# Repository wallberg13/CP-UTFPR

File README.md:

# CP-UTFPR

Este repositório é destinado a guardar todos os trabalhos e códigos
desenvolvidos ao longo da minha graduação em Engenharia de Computação na
UTFPR-PB.

> Pastas desorganizadas pois a organização veio com o tempo e o repositório
> ainda está um pouco bagunçando, mas com o tempo melhora.

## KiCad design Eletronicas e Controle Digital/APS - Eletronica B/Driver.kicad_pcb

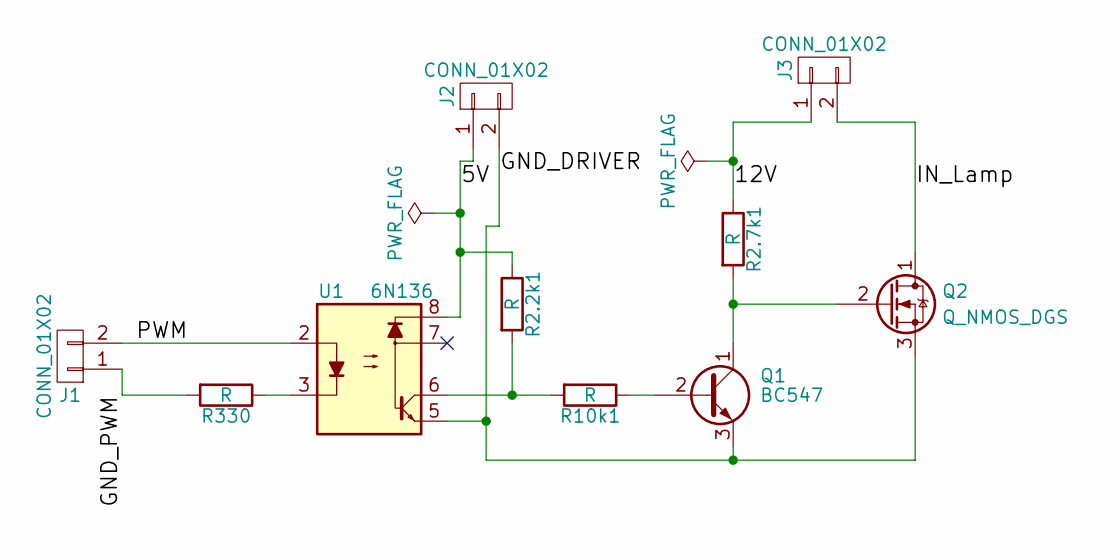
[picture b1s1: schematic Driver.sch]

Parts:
J1, J2, J3: CONN_01X02; bornier2
Q1: BC547; TO-92_Inline_Wide
Q2: Q_NMOS_DGS; Wafer_Vertical10x5.8x7RM2.5-3
R2.2k1, R2.7k1, R10k1, R330: R; R_Axial_DIN0309_L9.0mm_D3.2mm_P12.70mm_Horizontal
U1: 6N136; DIP-8_W7.62mm_Socket_LongPads

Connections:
/5V: J2.1, R2.2k1.1, U1.8
/12V: J3.1, R2.7k1.1
/GND_DRIVER: J2.2, Q1.3 (E), Q2.3 (S), U1.5
/GND_PWM: J1.1, R330.2
/IN_Lamp: J3.2, Q2.1 (D)
/PWM: J1.2, U1.2
unnamed: Q1.1 (C), Q2.2 (G), R2.7k1.2
unnamed: Q1.2 (B), R10k1.1
unnamed: R2.2k1.2, R10k1.2, U1.6
unnamed: R330.1, U1.3

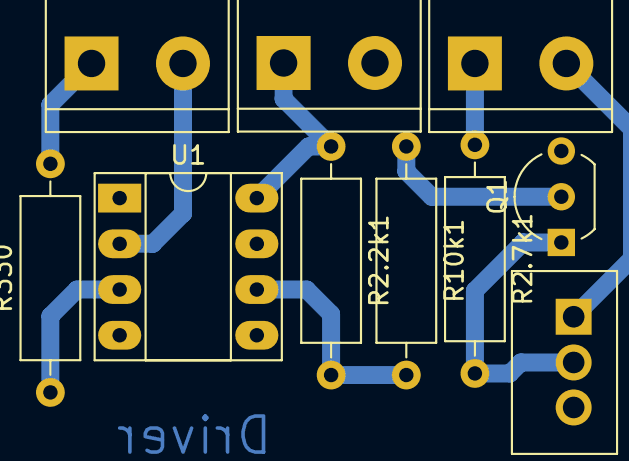
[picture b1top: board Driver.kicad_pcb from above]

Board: 2 copper layers, 10 parts (0 on the bottom side), 10 nets.

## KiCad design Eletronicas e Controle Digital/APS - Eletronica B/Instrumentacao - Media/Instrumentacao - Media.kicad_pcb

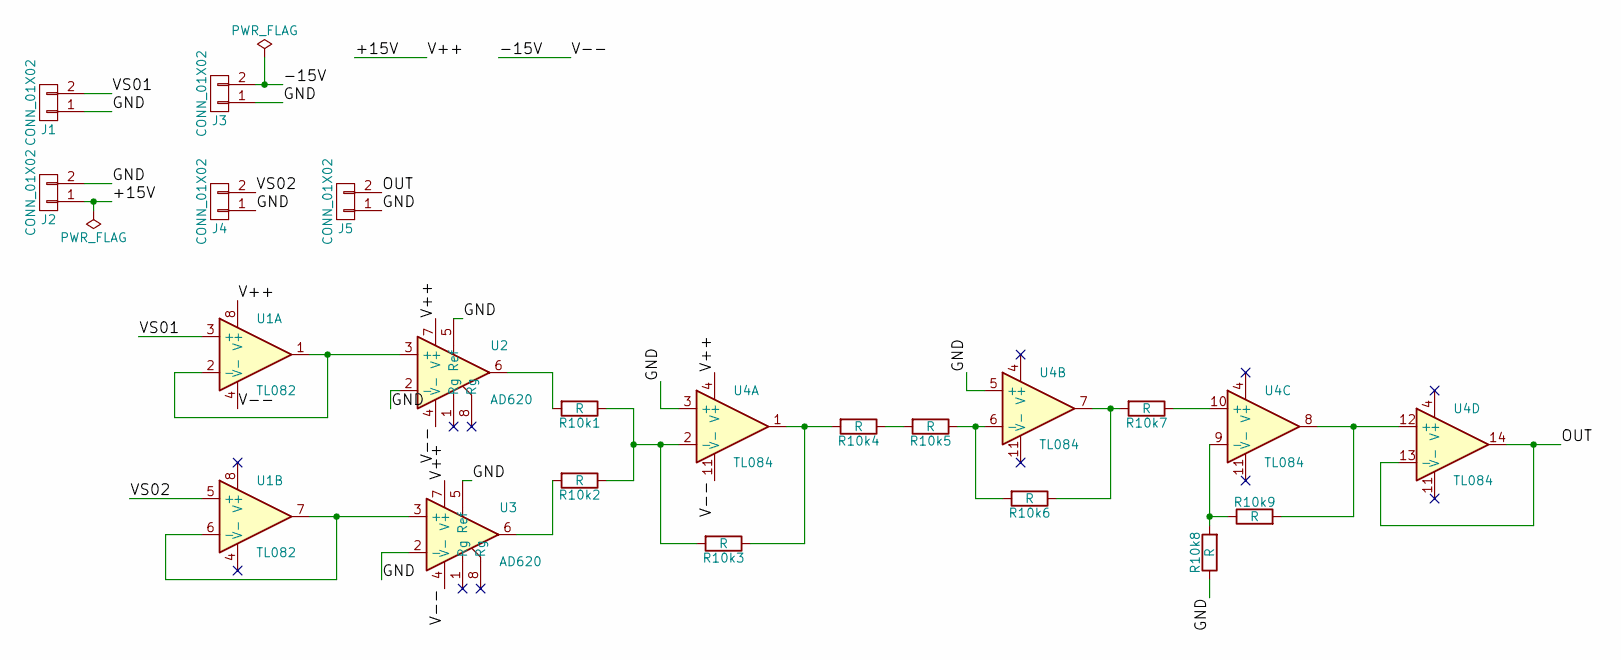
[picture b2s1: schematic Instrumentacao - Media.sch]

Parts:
J1, J2, J3, J4, J5: CONN_01X02; bornier2
R10k1, R10k2, R10k3, R10k4, R10k5, R10k6, R10k7, R10k8, R10k9: R; R_Axial_DIN0309_L9.0mm_D3.2mm_P12.70mm_Horizontal
U1: TL082; DIP-8_W7.62mm_Socket_LongPads
U2, U3: AD620; DIP-8_W7.62mm_Socket_LongPads
U4: TL084; DIP-14_W7.62mm_Socket_LongPads

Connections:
/+15V: J2.1, U1.8 (V+), U2.7 (V+), U3.7 (V+), U4.4 (V+)
/-15V: J3.2, U1.4 (V-), U2.4 (V-), U3.4 (V-), U4.11 (V-)
/GND: J1.1, J2.2, J3.1, J4.1, J5.1, R10k8.1, U2.2 (-), U2.5 (Ref), U3.2 (-), U3.5 (Ref), U4.3 (+), U4.5 (+)
/OUT: J5.2, U4.13 (-), U4.14
/VS01: J1.2, U1.3 (+)
/VS02: J4.2, U1.5 (+)
unnamed: R10k1.1, R10k2.1, R10k3.2, U4.2 (-)
unnamed: R10k1.2, U2.6
unnamed: R10k2.2, U3.6
unnamed: R10k3.1, R10k4.2, U4.1
unnamed: R10k4.1, R10k5.2
unnamed: R10k5.1, R10k6.2, U4.6 (-)
unnamed: R10k6.1, R10k7.2, U4.7
unnamed: R10k7.1, U4.10 (+)
unnamed: R10k8.2, R10k9.1, U4.9 (-)
unnamed: R10k9.2, U4.8, U4.12 (+)
unnamed: U1.1, U1.2 (-), U2.3 (+)
unnamed: U1.6 (-), U1.7, U3.3 (+)

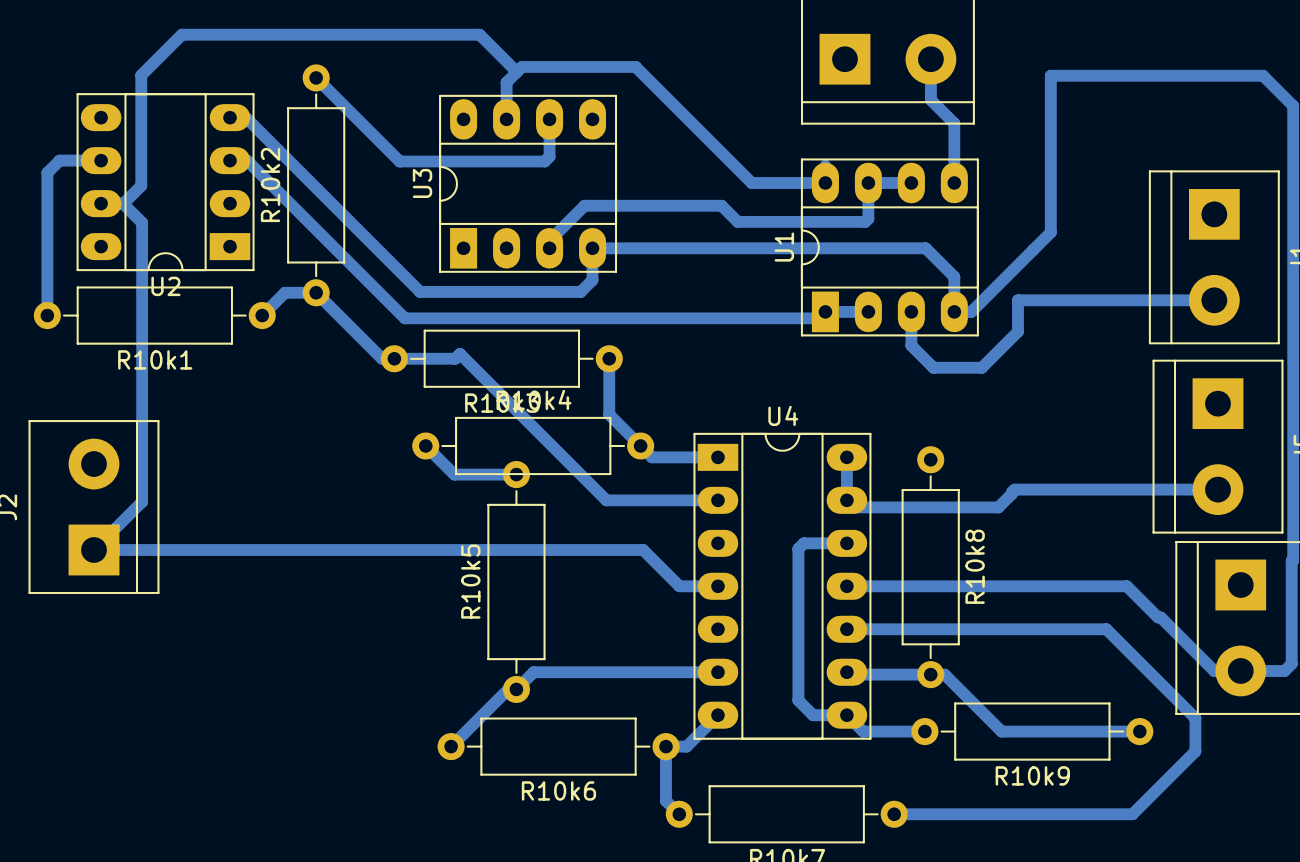
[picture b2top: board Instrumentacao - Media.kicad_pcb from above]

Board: 2 copper layers, 18 parts (0 on the bottom side), 18 nets.

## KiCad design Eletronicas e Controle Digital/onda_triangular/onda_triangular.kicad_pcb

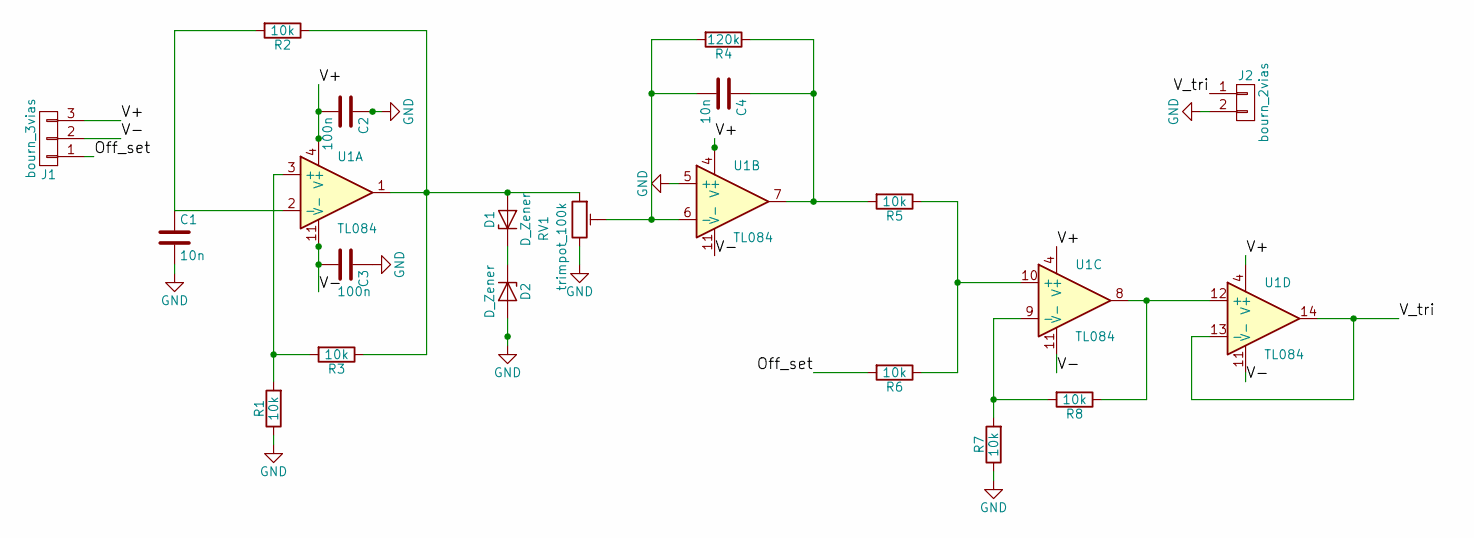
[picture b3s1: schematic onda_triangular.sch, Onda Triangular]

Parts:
C1, C4: 10n; C_Rect_L11.0mm_W6.3mm_P10.00mm_MKT
C2, C3: 100n; C_Rect_L11.0mm_W6.3mm_P10.00mm_MKT
D1, D2: D_Zener; D_DO-41_SOD81_P10.16mm_Horizontal
J1: bourn_3vias; bornier3
J2: bourn_2vias; bornier2
R1, R2, R3, R5, R6, R7, R8: 10k; R_Axial_DIN0207_L6.3mm_D2.5mm_P10.16mm_Horizontal
R4: 120k; R_Axial_DIN0207_L6.3mm_D2.5mm_P10.16mm_Horizontal
RV1: trimpot_100k; Potentiometer_Trimmer_Suntan_TSR-3386P_Horizontal
U1: TL084; DIP-14_W7.62mm_Socket_LongPads

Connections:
/Off_set: J1.1, R6.2
/V+: C2.2, J1.3, U1.4 (V+)
/V-: C3.2, J1.2, U1.11 (V-)
/V_tri: J2.1, U1.13 (-), U1.14
GND: C1.2, C2.1, C3.1, D2.2 (A), J2.2, R1.1, R7.1, RV1.3, U1.5 (+)
unnamed: C1.1, R2.2, U1.2 (-)
unnamed: C4.1, R4.1, R5.2, U1.7
unnamed: C4.2, R4.2, RV1.2, U1.6 (-)
unnamed: D1.1 (K), D2.1 (K)
unnamed: D1.2 (A), R2.1, R3.1, RV1.1, U1.1
unnamed: R1.2, R3.2, U1.3 (+)
unnamed: R5.1, R6.1, U1.10 (+)
unnamed: R7.2, R8.2, U1.9 (-)
unnamed: R8.1, U1.8, U1.12 (+)

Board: 2 copper layers, 18 parts (0 on the bottom side), 14 nets, no tracks yet.

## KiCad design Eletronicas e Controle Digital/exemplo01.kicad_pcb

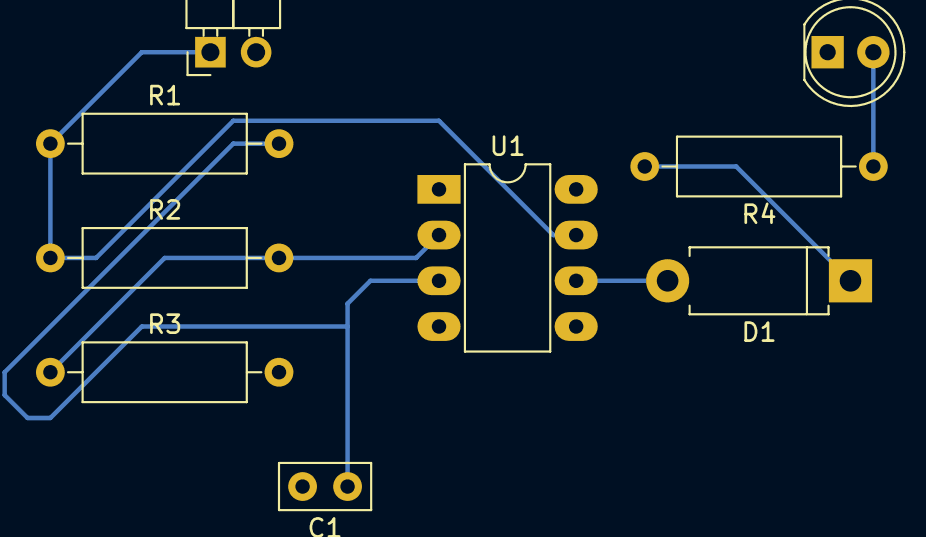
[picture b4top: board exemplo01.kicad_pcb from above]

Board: 2 copper layers, 9 parts (0 on the bottom side), 7 nets.

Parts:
C1: C; C_Disc_D5.0mm_W2.5mm_P2.50mm
D1: D; D_DO-15_P10.16mm_Horizontal
D2: LED; LED_D5.0mm
J1: CONN_01X02; Pin_Header_Angled_1x02_Pitch2.54mm
R1, R2, R3, R4: R; R_Axial_DIN0309_L9.0mm_D3.2mm_P12.70mm_Horizontal
U1: LM741; DIP-8_W7.62mm_LongPads

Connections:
Earth: C1.2, D2.1, J1.2, R3.2, U1.4
unnamed: C1.1, R1.2, U1.3
unnamed: D1.1, R4.2
unnamed: D1.2, U1.6
unnamed: D2.2, R4.1
unnamed: J1.1, R1.1, R2.1, U1.7
unnamed: R2.2, R3.1, U1.2

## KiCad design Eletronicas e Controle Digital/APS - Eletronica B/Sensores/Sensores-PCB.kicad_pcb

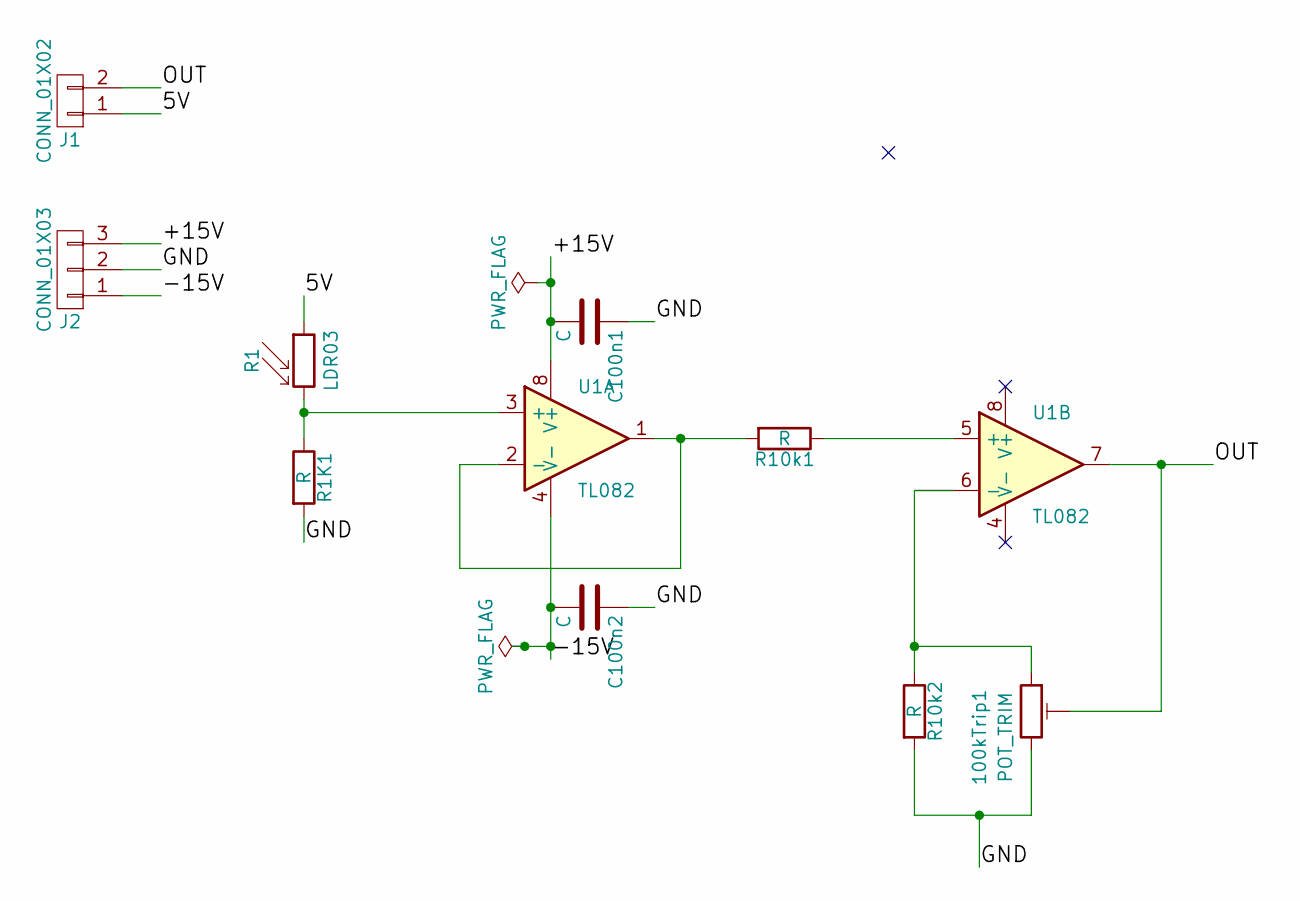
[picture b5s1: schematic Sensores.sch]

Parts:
100kTrip1: POT_TRIM; Potentiometer_Trimmer_Suntan_TSR-3386P_Horizontal
C100n1, C100n2: C; C_Rect_L10.3mm_W5.0mm_P7.50mm_MKS4
J1: CONN_01X02; bornier2
J2: CONN_01X03; bornier3
R1: LDR03; Resistor_LDR_10x8.5_RM7.6
R1K1, R10k1, R10k2: R; R_Axial_DIN0309_L9.0mm_D3.2mm_P12.70mm_Horizontal
U1: TL082; DIP-8_W7.62mm_Socket_LongPads

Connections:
/5V: J1.1, R1.1
/+15V: C100n1.2, J2.3, U1.8 (V+)
/-15V: C100n2.2, J2.1, U1.4 (V-)
/GND: 100kTrip1.3, C100n1.1, C100n2.1, J2.2, R1K1.2, R10k2.2
/OUT: 100kTrip1.2, J1.2, U1.7
unnamed: 100kTrip1.1, R10k2.1, U1.6 (-)
unnamed: R1.2, R1K1.1, U1.3 (+)
unnamed: R10k1.1, U1.5 (+)
unnamed: R10k1.2, U1.1, U1.2 (-)

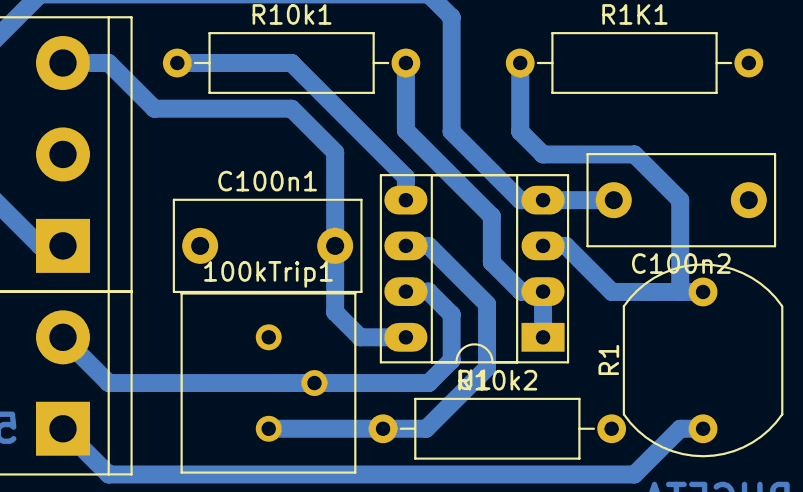
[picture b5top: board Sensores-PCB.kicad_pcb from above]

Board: 2 copper layers, 10 parts (0 on the bottom side), 9 nets.

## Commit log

2018-04-14 Primeiro commit
2018-04-14 Segundo commit
2018-04-17 Adicionando conteudos de uCon, Logica Reconfiguravel, Eletronicas e Controle digital
2018-04-25 Create LICENSE
2018-06-07 Adicionando atividades já entregue de sistemas distribuidos
2018-08-15 Nao sei o que deu com a pasta de projetos
2018-09-02 Permissoes do Capeta
2018-09-20 Nao lembro o que fiz
2018-12-20 Adicionando materia de desenvolvimentos movéis
2019-04-27 Add Sistemas de Controle2.zip - Final Commit
